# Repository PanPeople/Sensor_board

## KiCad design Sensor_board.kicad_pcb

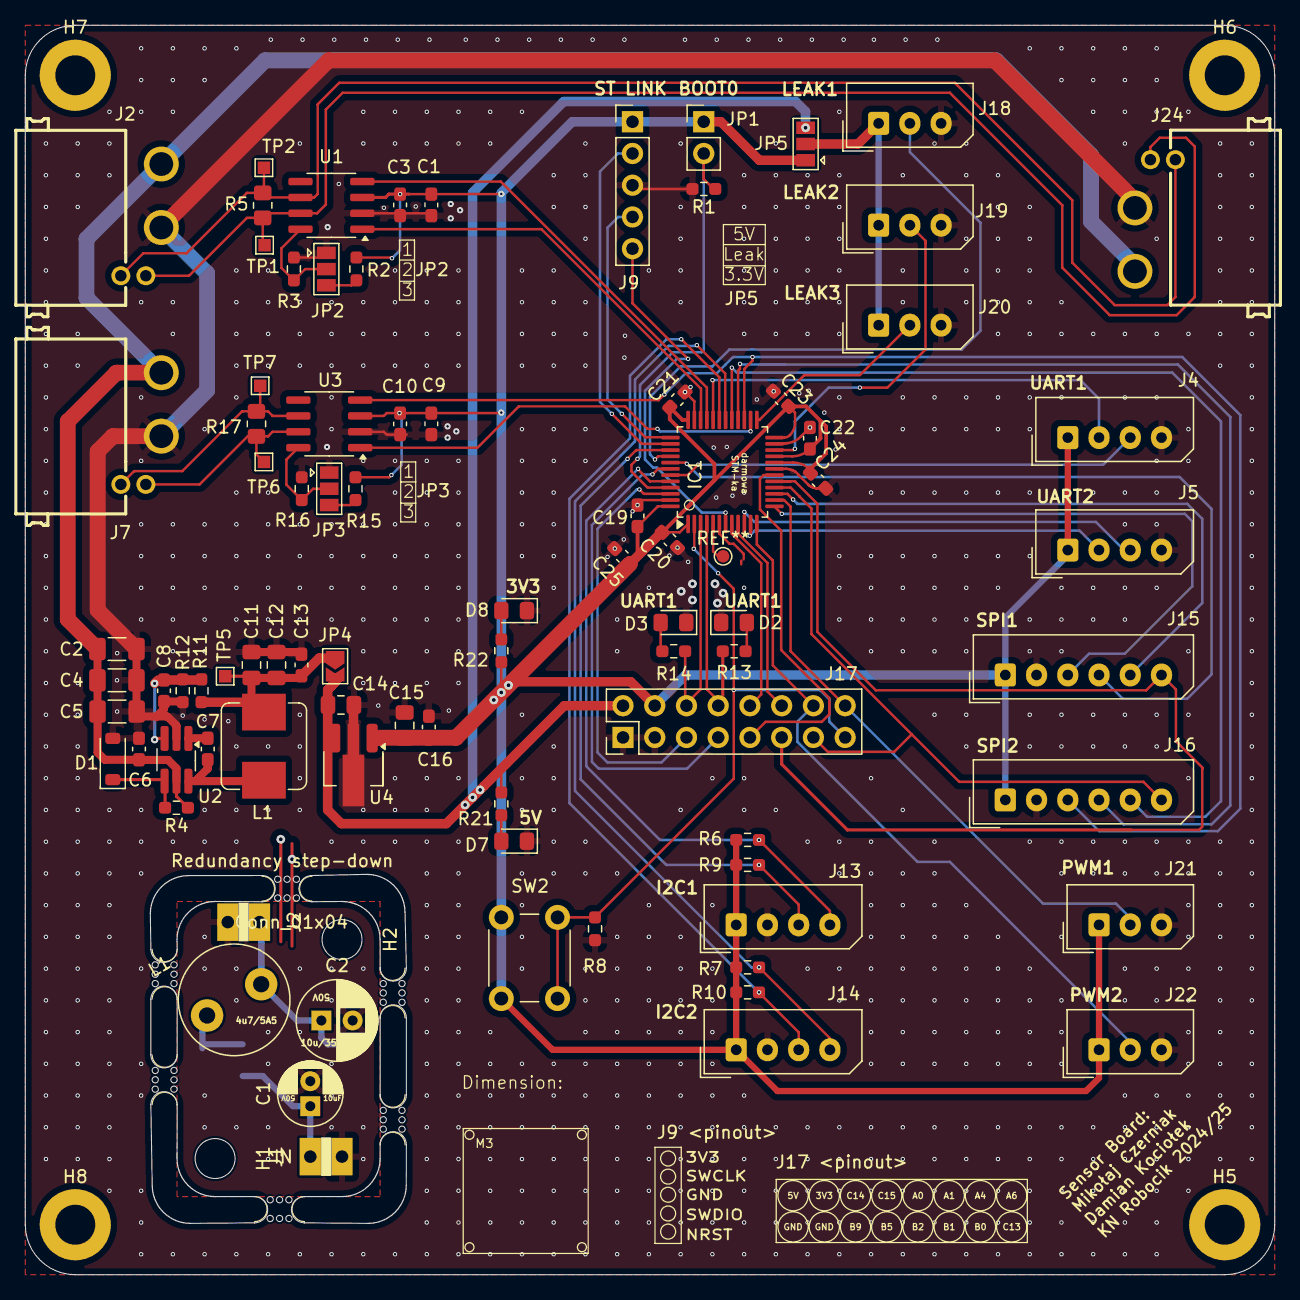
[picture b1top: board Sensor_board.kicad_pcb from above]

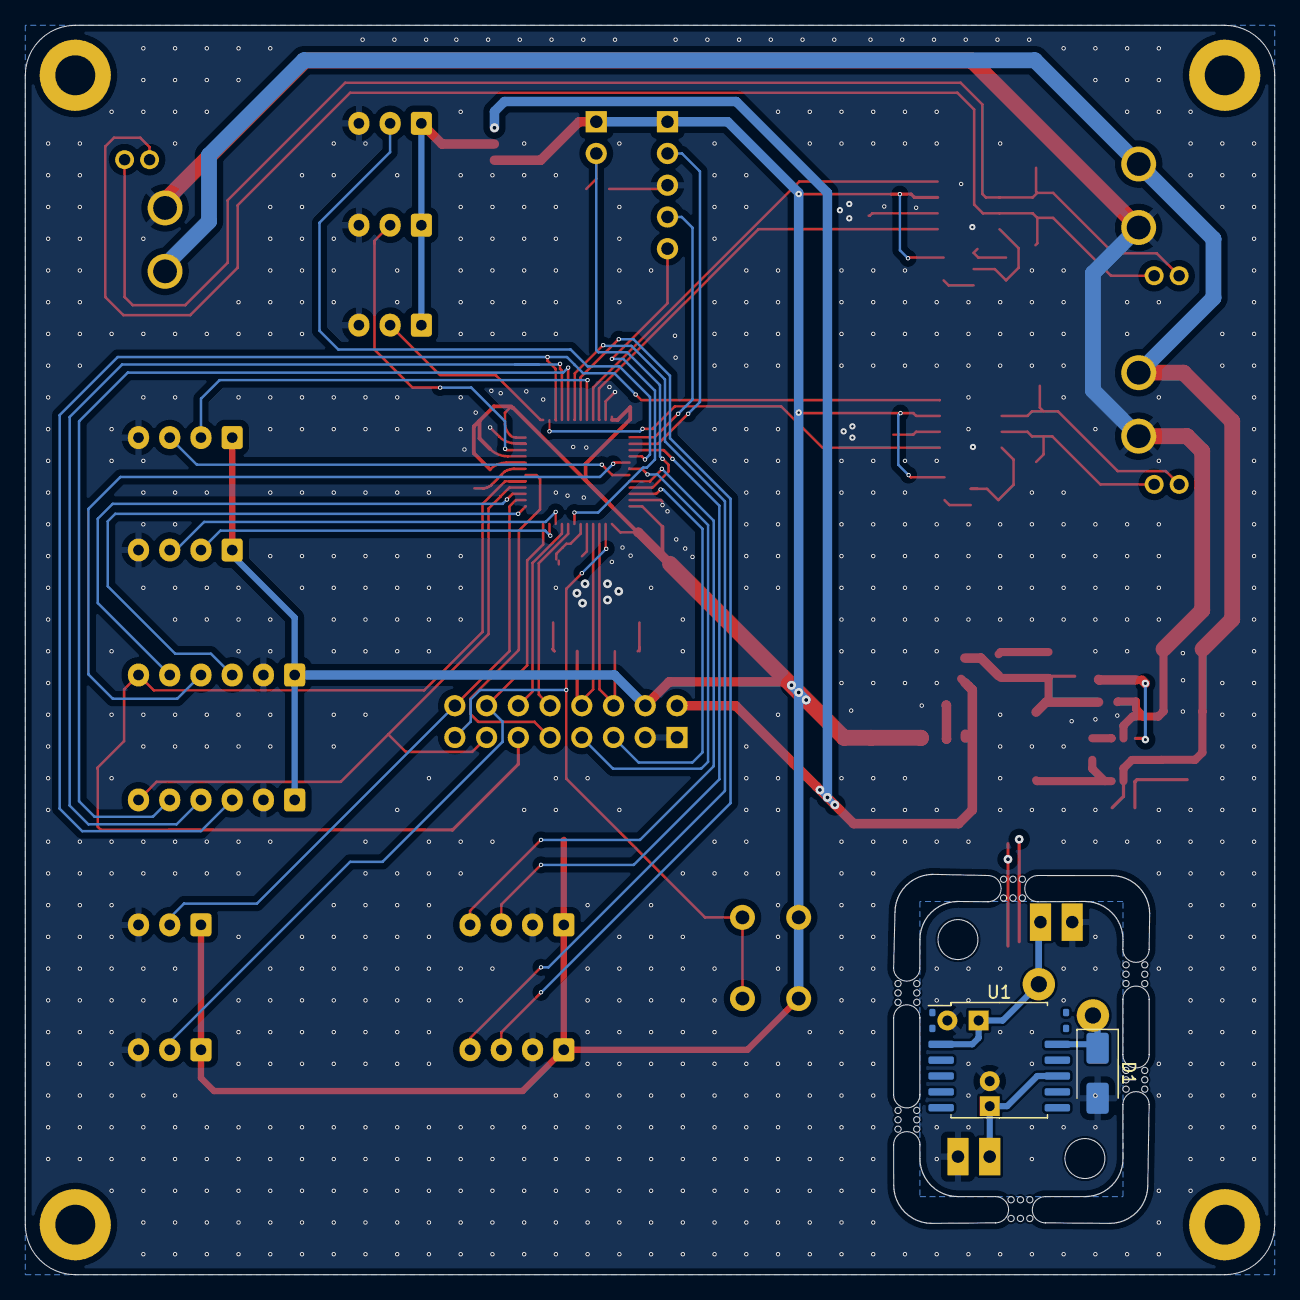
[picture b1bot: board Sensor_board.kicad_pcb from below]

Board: 2 copper layers, 100.0 x 99.9 mm, 99 parts (2 on the bottom side), 58 nets.

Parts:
C1: 10uF; CP_Radial_D5.0mm_P2.00mm
C1#2, C9: 10uF; C_0603_1608Metric_Pad1.08x0.95mm_HandSolder
C2: 10u/35V; CP_Radial_D6.3mm_P2.50mm
C2#2, C4, C5: 10u/35V; C_1206_3216Metric_Pad1.33x1.80mm_HandSolder
C3, C10, C19, C20, C21, C22, C23, C24: 100nF; C_0603_1608Metric_Pad1.08x0.95mm_HandSolder
C6, C7, C13, C16: 100n/50V; C_0603_1608Metric_Pad1.08x0.95mm_HandSolder
C8: 22p/25V; C_0603_1608Metric_Pad1.08x0.95mm_HandSolder
C11, C12, C14, C15: 22u/10V; C_0805_2012Metric_Pad1.18x1.45mm_HandSolder
C25: 4.7uF; C_0603_1608Metric_Pad1.08x0.95mm_HandSolder
D1: 5V; D_SOD-123
D1#2: 5V; D_SMA
D2, D3, D7, D8: LED_0805_2012Metric_Pad1.15x1.40mm_HandSolder
H1, H2: MountingHole; MountingHole_3.2mm_M3_ISO7380
H5, H6, H7, H8: MountingHole; MountingHole_3.2mm_M3_ISO7380_Pad
IC1: STM32G491CET6; LQFP-48_7x7mm_P0.5mm
J1: IN; PinSocket_1x02_P2.54mm_Vertical
J2: Conn_01x04; PinSocket_1x02_P2.54mm_Vertical
J2#2, J7, J24: Conn_01x04; CONN-TH_4P-XT30PW-M
J4, J5, J13, J14: Conn_01x04; Molex_SPOX_5267-04A_1x04_P2.50mm_Vertical
J9: Conn_01x05; PinHeader_1x05_P2.54mm_Vertical
J15, J16: Conn_01x06; Molex_SPOX_5267-06A_1x06_P2.50mm_Vertical
J17: Conn_02x08_Odd_Even; PinHeader_2x08_P2.54mm_Vertical
J18, J19, J20, J21, J22: Conn_01x03; Molex_SPOX_5267-03A_1x03_P2.50mm_Vertical
JP1: Jumper_2_Open; PinHeader_1x02_P2.54mm_Vertical
JP2, JP3, JP5: SolderJumper_3_Open; SolderJumper-3_P1.3mm_Open_Pad1.0x1.5mm
JP4: SolderJumper_2_Bridged; SolderJumper-2_P1.3mm_Open_TrianglePad1.0x1.5mm
L1: 4u7/5A5; L_Bourns_SRP7028A_7.3x6.6mm
L1#2: 4u7/5A5; L_Radial_D8.7mm_P5.00mm_Fastron_07HCP
R1, R11: 100k; R_0603_1608Metric_Pad0.98x0.95mm_HandSolder
R2, R15: 2k2; R_0603_1608Metric_Pad0.98x0.95mm_HandSolder
R3, R6, R7, R8, R9, R10, R16: 10k; R_0603_1608Metric_Pad0.98x0.95mm_HandSolder
R4: 10K; R_0603_1608Metric_Pad0.98x0.95mm_HandSolder
R5, R17: 120R; R_0805_2012Metric_Pad1.20x1.40mm_HandSolder
R12: 22k; R_0603_1608Metric_Pad0.98x0.95mm_HandSolder
R13, R14, R21: 1k; R_0603_1608Metric_Pad0.98x0.95mm_HandSolder
R22: 120; R_0603_1608Metric_Pad0.98x0.95mm_HandSolder
SW2: SW_Push; SW_PUSH_6mm
TP1, TP2, TP5, TP6, TP7: TestPoint; TestPoint_Pad_1.0x1.0mm
U1, U3: SN65HVD230; SOIC-8_3.9x4.9mm_P1.27mm
U1#2: SN65HVD230; SOIC-14W_7.5x9mm_P1.27mm
U2: DIO6913; TSOT-23-6_HandSoldering
U4: L78L33_SOT89; SOT-89-3_Handsoldering
mouse-bite-2mm-slot, mouse-bite-2mm-slot#2, mouse-bite-2mm-slot#3, mouse-bite-2mm-slot#4, mouse-bite-2mm-slot#5, mouse-bite-2mm-slot#6: VAL**; mouse-bite-2mm-slot

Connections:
+3.3V: C1.1, C1#2.1, C3.1, C9.1, C10.1, C15.1, C16.2, C19.1, C20.1, C21.1, C22.1, C23.1, C24.1, C25.1, IC1.1 (VBAT), IC1.20 (VREF+), IC1.21 (VDDA), IC1.24 (VDD_1), IC1.36 (VDD_2), IC1.48 (VDD_3), J4.1, J5.1, J9.1, J13.1, J14.1, J15.1, J16.1, J17.4, J21.1, J22.1, JP1.1 (A), JP5.1 (A), R2.1, R6.1, R7.1, R9.1, R10.1, R15.1, R22.1, SW2.2, U1.3 (VCC), U1#2.3 (VCC), U3.3 (VCC), U4.1 (OUT)
+5V: C14.1, J17.2, JP4.2 (B), JP5.3 (B), R21.1, U4.3 (IN)
/ADC1_IN1: IC1.8 (PA0), J17.10
/ADC1_IN2: IC1.9 (PA1), J17.12
/BATT: C2.1, C2#2.1, C4.1, C5.1, C6.2, J2.1, J2#2.1, J7.1, J24.1, R4.1, U2.5 (VIN)
/BOOT0: IC1.45 (PB8-BOOT0), JP1.2 (B), R1.1
/CAN_1_H: J2#2.3, J24.3, R5.1, TP1.1, U1.7 (CANH), U1#2.7 (CANH)
/CAN_1_L: J2#2.4, J24.4, R5.2, TP2.1, U1.6 (CANL), U1#2.6 (CANL)
/CAN_2_H: J7.3, R17.1, TP6.1, U3.7 (CANH)
/CAN_2_L: J7.4, R17.2, TP7.1, U3.6 (CANL)
/FDCAN1_RX: IC1.33 (PA11), U1.4 (R), U1#2.4 (R)
/FDCAN1_TX: IC1.34 (PA12), U1.1 (D), U1#2.1 (D)
/FDCAN2_RX: IC1.27 (PB13), J16.3, U3.4 (R)
/FDCAN2_TX: IC1.26 (PB12), U3.1 (D)
/I2C1_SCL: IC1.39 (PA15), J13.3, R9.2
/I2C1_SDA: IC1.44 (PB7), J13.4, R6.2
/I2C2_SCL: IC1.31 (PA9), J14.3, R10.2
/I2C2_SDA: IC1.30 (PA8), J14.4, R7.2
/NRST: IC1.7 (PG10_-_NRST), J9.5
/PA4: IC1.12 (PA4), J17.14, J22.2
/PA6: IC1.14 (PA6), J17.16, J21.2
/PB0: IC1.16 (PB0), J16.6, J17.13
/PB1: IC1.17 (PB1), J15.6, J17.11
/PB2: IC1.18 (PB2), J17.9
/PB5: IC1.42 (PB5), J17.7
/PB9: IC1.46 (PB9), J17.5
/PC13: IC1.2 (PC13), J17.15, R8.1, SW2.1
/PC14: IC1.3 (PC14_-_OSC32_IN), J17.6, R14.1
/PC15: IC1.4 (PC15_-_OSC32_OUT), J17.8, R13.1
/SPI1_MISO: IC1.41 (PB4), J15.4
/SPI1_MOSI: IC1.15 (PA7), J15.5
/SPI1_SCK: IC1.13 (PA5), J15.3
/SPI2_MISO: IC1.28 (PB14), J16.4
/SPI2_MOSI: IC1.29 (PB15), J16.5
/SWCLK: IC1.38 (PA14), J9.2
/SWDIO: IC1.37 (PA13), J9.4
/TIM2_CH2: IC1.40 (PB3), J18.2
/TIM2_CH3: IC1.22 (PB10), J19.2
/TIM2_CH4: IC1.25 (PB11), J20.2
/USART1_RX: IC1.32 (PA10), J4.2
/USART1_TX: IC1.43 (PB6), J4.3
/USART2_RX: IC1.11 (PA3), J5.2
/USART2_TX: IC1.10 (PA2), J5.3
GND: C1.2, C1#2.2, C2.2, C2#2.2, C3.2, C4.2, C5.2, C6.1, C8.2, C9.2, C10.2, C11.2, C12.2, C13.1, C14.2, C15.2, C16.1, C19.2, C20.2, C21.2, C22.2, C23.2, C24.2, C25.2, D1.2 (A), D1#2.2 (A), D2.1 (K), D3.1 (K), D7.1 (K), D8.1 (K), IC1.19 (VSSA), IC1.23 (VSS_1), IC1.35 (VSS_2), IC1.47 (VSS_3), J1.2, J2.2, J2#2.2, J4.4, J5.4, J7.2, J9.3, J13.2, J14.2, J15.2, J16.2, J17.1, J17.3, J18.3, J19.3, J20.3, J21.3, J22.3, J24.2, JP2.1 (A), JP3.1 (A), R1.2, R3.1, R8.2, R12.2, R16.1, U1.2 (GND), U1#2.2 (GND), U2.2 (GND), U3.2 (GND), U4.2 (GND)
unnamed: D1.1 (K), D1#2.1 (K), R4.2, U2.4 (EN)
unnamed: D2.2 (A), R13.2
unnamed: D3.2 (A), R14.2
unnamed: D7.2 (A), R21.2
unnamed: D8.2 (A), R22.2
unnamed: J18.1, J19.1, J20.1, JP5.2 (C)
unnamed: JP2.3 (B), R2.2
unnamed: JP2.2 (C), R3.2, U1.8 (Rs), U1#2.8 (Rs)
unnamed: JP3.3 (B), R15.2
unnamed: JP3.2 (C), R16.2, U3.8 (Rs)
unnamed: C11.1, C12.1, C13.2, JP4.1 (A), L1.2, L1#2.2, R11.1, TP5.1
unnamed: C7.2, U2.1 (BS)
unnamed: C8.1, R11.2, R12.1, U2.3 (FB)
unnamed: C7.1, L1.1, L1#2.1, U2.6 (LX)

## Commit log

2024-12-22 changed mcu pinout
2024-12-29 50% of trace
2024-12-29 60% of trace
2025-01-27 almost done
2025-01-29 Ready for review from Mr Kettle
2025-01-29 Updated silkscreen
2025-02-24 major route chanses to improve overall layout
2025-02-27 final design version
